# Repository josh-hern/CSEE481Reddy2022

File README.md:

# CSEE481Reddy2022
Group repo for WVU capstone 2022

## infrastructure

Contains the database, REST API, and business logic. Implemented in Python.

## hardware

Contains the main board PCB, ESP 32 symbol library, and 3D files.

## webview

Contains the web application that will be used to server web clients of the
battleship game.

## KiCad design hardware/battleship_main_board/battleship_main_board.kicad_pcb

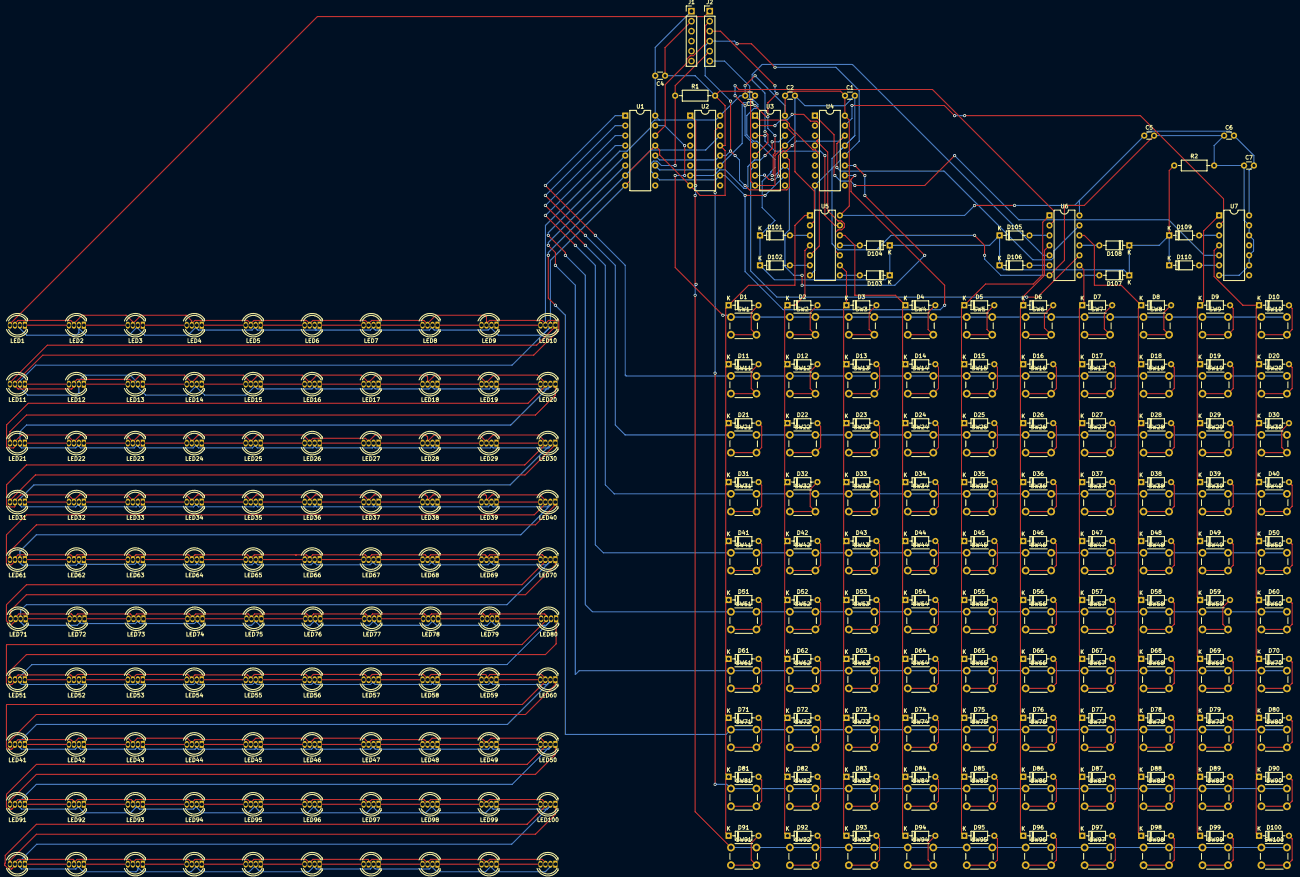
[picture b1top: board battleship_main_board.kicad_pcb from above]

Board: 2 copper layers, 328 parts (0 on the bottom side), 248 nets.

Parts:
C1, C2, C3, C4, C5, C6, C7: 0.1uf; C_Disc_D3.0mm_W1.6mm_P2.50mm
D1, D2, D3, D4, D5, D6, D7, D8, D9, D10, D11, D12, D13, D14, D15, D16, D17, D18, D19, D20, D21, D22, D23, D24, D25, D26, D27, D28, D29, D30, D31, D32, D33, D34, D35, D36, D37, D38, D39, D40, D41, D42, D43, D44, D45, D46, D47, D48, D49, D50, D51, D52, D53, D54, D55, D56, D57, D58, D59, D60, D61, D62, D63, D64, D65, D66, D67, D68, D69, D70, D71, D72, D73, D74, D75, D76, D77, D78, D79, D80, D81, D82, D83, D84, D85, D86, D87, D88, D89, D90, D91, D92, D93, D94, D95, D96, D97, D98, D99, D100, D101, D102, D103, D104, D105, D106, D107, D108, D109, D110: 1N4148; D_DO-35_SOD27_P7.62mm_Horizontal
J1, J2: Conn_01x06; PinHeader_1x06_P2.54mm_Vertical
LED1, LED2, LED3, LED4, LED5, LED6, LED7, LED8, LED9, LED10, LED11, LED12, LED13, LED14, LED15, LED16, LED17, LED18, LED19, LED20, LED21, LED22, LED23, LED24, LED25, LED26, LED27, LED28, LED29, LED30, LED31, LED32, LED33, LED34, LED35, LED36, LED37, LED38, LED39, LED40, LED41, LED42, LED43, LED44, LED45, LED46, LED47, LED48, LED49, LED50, LED51, LED52, LED53, LED54, LED55, LED56, LED57, LED58, LED59, LED60, LED61, LED62, LED63, LED64, LED65, LED66, LED67, LED68, LED69, LED70, LED71, LED72, LED73, LED74, LED75, LED76, LED77, LED78, LED79, LED80, LED81, LED82, LED83, LED84, LED85, LED86, LED87, LED88, LED89, LED90, LED91, LED92, LED93, LED94, LED95, LED96, LED97, LED98, LED99, LED100: WS2812B; LED_D5.0mm-4_RGB
R1, R2: 1k; R_Axial_DIN0207_L6.3mm_D2.5mm_P10.16mm_Horizontal
SW1, SW2, SW3, SW4, SW5, SW6, SW7, SW8, SW9, SW10, SW11, SW12, SW13, SW14, SW15, SW16, SW17, SW18, SW19, SW20, SW21, SW22, SW23, SW24, SW25, SW26, SW27, SW28, SW29, SW30, SW31, SW32, SW33, SW34, SW35, SW36, SW37, SW38, SW39, SW40, SW41, SW42, SW43, SW44, SW45, SW46, SW47, SW48, SW49, SW50, SW51, SW52, SW53, SW54, SW55, SW56, SW57, SW58, SW59, SW60, SW61, SW62, SW63, SW64, SW65, SW66, SW67, SW68, SW69, SW70, SW71, SW72, SW73, SW74, SW75, SW76, SW77, SW78, SW79, SW80, SW81, SW82, SW83, SW84, SW85, SW86, SW87, SW88, SW89, SW90, SW91, SW92, SW93, SW94, SW95, SW96, SW97, SW98, SW99, SW100: SW_Push; SW_PUSH_6mm
U1, U2, U3, U4: 74HC595; DIP-16_W7.62mm
U5, U6, U7: 74LS08; DIP-14_W7.62mm

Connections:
+5V: C1.1, C2.1, C3.2, C4.2, C5.1, C6.2, C7.2, J1.1, LED1.3 (VDD), LED2.3 (VDD), LED3.3 (VDD), LED4.3 (VDD), LED5.3 (VDD), LED6.3 (VDD), LED7.3 (VDD), LED8.3 (VDD), LED9.3 (VDD), LED10.3 (VDD), LED11.3 (VDD), LED12.3 (VDD), LED13.3 (VDD), LED14.3 (VDD), LED15.3 (VDD), LED16.3 (VDD), LED17.3 (VDD), LED18.3 (VDD), LED19.3 (VDD), LED20.3 (VDD), LED21.3 (VDD), LED22.3 (VDD), LED23.3 (VDD), LED24.3 (VDD), LED25.3 (VDD), LED26.3 (VDD), LED27.3 (VDD), LED28.3 (VDD), LED29.3 (VDD), LED30.3 (VDD), LED31.3 (VDD), LED32.3 (VDD), LED33.3 (VDD), LED34.3 (VDD), LED35.3 (VDD), LED36.3 (VDD), LED37.3 (VDD), LED38.3 (VDD), LED39.3 (VDD), LED40.3 (VDD), LED41.3 (VDD), LED42.3 (VDD), LED43.3 (VDD), LED44.3 (VDD), LED45.3 (VDD), LED46.3 (VDD), LED47.3 (VDD), LED48.3 (VDD), LED49.3 (VDD), LED50.3 (VDD), LED51.3 (VDD), LED52.3 (VDD), LED53.3 (VDD), LED54.3 (VDD), LED55.3 (VDD), LED56.3 (VDD), LED57.3 (VDD), LED58.3 (VDD), LED59.3 (VDD), LED60.3 (VDD), LED61.3 (VDD), LED62.3 (VDD), LED63.3 (VDD), LED64.3 (VDD), LED65.3 (VDD), LED66.3 (VDD), LED67.3 (VDD), LED68.3 (VDD), LED69.3 (VDD), LED70.3 (VDD), LED71.3 (VDD), LED72.3 (VDD), LED73.3 (VDD), LED74.3 (VDD), LED75.3 (VDD), LED76.3 (VDD), LED77.3 (VDD), LED78.3 (VDD), LED79.3 (VDD), LED80.3 (VDD), LED81.3 (VDD), LED82.3 (VDD), LED83.3 (VDD), LED84.3 (VDD), LED85.3 (VDD), LED86.3 (VDD), LED87.3 (VDD), LED88.3 (VDD), LED89.3 (VDD), LED90.3 (VDD), LED91.3 (VDD), LED92.3 (VDD), LED93.3 (VDD), LED94.3 (VDD), LED95.3 (VDD), LED96.3 (VDD), LED97.3 (VDD), LED98.3 (VDD), LED99.3 (VDD), LED100.3 (VDD), U1.16 (VCC), U2.16 (VCC), U3.16 (VCC), U4.16 (VCC), U5.14 (VCC), U6.14 (VCC), U7.14 (VCC)
/ESP32/ButtonPressedIn: D101.1 (K), D102.1 (K), D103.1 (K), D104.1 (K), D105.1 (K), D106.1 (K), D107.1 (K), D108.1 (K), D109.1 (K), D110.1 (K), J2.6, R2.1
/ESP32/Clr: J2.5, R1.1, U1.10 (~SRCLR), U2.10 (~SRCLR), U3.10 (~SRCLR), U4.10 (~SRCLR)
/ESP32/LED_out: J2.1, LED1.4 (DIN)
/ESP32/RegClock: J2.4, U1.12 (RCLK), U2.12 (RCLK), U3.12 (RCLK), U4.12 (RCLK)
/ESP32/SerialOutput: J2.2, U1.14 (SER)
/ESP32/ShiftClock: J2.3, U1.11 (SRCLK), U2.11 (SRCLK), U3.11 (SRCLK), U4.11 (SRCLK)
/OutputMatrix1/TenLEDRow1/Row_data_out: LED20.1 (DOUT), LED21.4 (DIN)
/OutputMatrix1/TenLEDRow2/Row_data_out: LED30.1 (DOUT), LED31.4 (DIN)
/OutputMatrix1/TenLEDRow3/Row_data_out: LED40.1 (DOUT), LED61.4 (DIN)
/OutputMatrix1/TenLEDRow4/Row_data_in: LED41.4 (DIN), LED60.1 (DOUT)
/OutputMatrix1/TenLEDRow4/Row_data_out: LED50.1 (DOUT), LED91.4 (DIN)
/OutputMatrix1/TenLEDRow5/Row_data_in: LED51.4 (DIN), LED80.1 (DOUT)
/OutputMatrix1/TenLEDRow6/Row_data_out: LED70.1 (DOUT), LED71.4 (DIN)
/OutputMatrix1/TenLEDRow8/Row_data_in: LED81.4 (DIN), LED100.1 (DOUT)
/OutputMatrix1/TenLEDRow/Row_data_out: LED10.1 (DOUT), LED11.4 (DIN)
/UserInputs/InputMatrix1/Button Row1/ColumnIn3: D4.1 (K), D14.1 (K), D24.1 (K), D34.1 (K), D44.1 (K), D54.1 (K), D64.1 (K), D74.1 (K), D84.1 (K), D94.1 (K), U5.12
/UserInputs/InputMatrix1/Button Row1/ColumnIn4: D5.1 (K), D15.1 (K), D25.1 (K), D35.1 (K), D45.1 (K), D55.1 (K), D65.1 (K), D75.1 (K), D85.1 (K), D95.1 (K), U6.1
/UserInputs/InputMatrix1/Button Row1/ColumnIn5: D6.1 (K), D16.1 (K), D26.1 (K), D36.1 (K), D46.1 (K), D56.1 (K), D66.1 (K), D76.1 (K), D86.1 (K), D96.1 (K), U6.4
/UserInputs/InputMatrix1/Button Row1/ColumnIn6: D7.1 (K), D17.1 (K), D27.1 (K), D37.1 (K), D47.1 (K), D57.1 (K), D67.1 (K), D77.1 (K), D87.1 (K), D97.1 (K), U6.9
/UserInputs/InputMatrix1/Button Row1/ColumnIn8: D9.1 (K), D19.1 (K), D29.1 (K), D39.1 (K), D49.1 (K), D59.1 (K), D69.1 (K), D79.1 (K), D89.1 (K), D99.1 (K), U7.1
/UserInputs/InputMatrix1/Button Row1/ColumnIn9: D10.1 (K), D20.1 (K), D30.1 (K), D40.1 (K), D50.1 (K), D60.1 (K), D70.1 (K), D80.1 (K), D90.1 (K), D100.1 (K), U7.4
/UserInputs/InputMatrix1/Button Row1/ColumnOut0: D1.1 (K), D11.1 (K), D21.1 (K), D31.1 (K), D41.1 (K), D51.1 (K), D61.1 (K), D71.1 (K), D81.1 (K), D91.1 (K), U5.1
/UserInputs/InputMatrix1/Button Row1/ColumnOut1: D2.1 (K), D12.1 (K), D22.1 (K), D32.1 (K), D42.1 (K), D52.1 (K), D62.1 (K), D72.1 (K), D82.1 (K), D92.1 (K), U5.4
/UserInputs/InputMatrix1/Button Row1/ColumnOut2: D3.1 (K), D13.1 (K), D23.1 (K), D33.1 (K), D43.1 (K), D53.1 (K), D63.1 (K), D73.1 (K), D83.1 (K), D93.1 (K), U5.9
/UserInputs/InputMatrix1/Button Row1/ColumnOut7: D8.1 (K), D18.1 (K), D28.1 (K), D38.1 (K), D48.1 (K), D58.1 (K), D68.1 (K), D78.1 (K), D88.1 (K), D98.1 (K), U6.12
/UserInputs/InputMatrix1/Col0: U3.15 (QA), U5.2
/UserInputs/InputMatrix1/Col1: U3.1 (QB), U5.5
/UserInputs/InputMatrix1/Col2: U3.2 (QC), U5.10
/UserInputs/InputMatrix1/Col3: U3.3 (QD), U5.13
/UserInputs/InputMatrix1/Col4: U3.4 (QE), U6.2
/UserInputs/InputMatrix1/Col5: U3.5 (QF), U6.5
/UserInputs/InputMatrix1/Col6: U3.6 (QG), U6.10
/UserInputs/InputMatrix1/Col7: U3.7 (QH), U4.14 (SER), U6.13
/UserInputs/InputMatrix1/Col8: U4.15 (QA), U7.2
/UserInputs/InputMatrix1/Col9: U4.1 (QB), U7.5
/UserInputs/InputMatrix1/Row0: SW1.1, SW2.1, SW3.1, SW4.1, SW5.1, SW6.1, SW7.1, SW8.1, SW9.1, SW10.1, U1.15 (QA)
/UserInputs/InputMatrix1/Row1: SW11.1, SW12.1, SW13.1, SW14.1, SW15.1, SW16.1, SW17.1, SW18.1, SW19.1, SW20.1, U1.1 (QB)
/UserInputs/InputMatrix1/Row2: SW21.1, SW22.1, SW23.1, SW24.1, SW25.1, SW26.1, SW27.1, SW28.1, SW29.1, SW30.1, U1.2 (QC)
/UserInputs/InputMatrix1/Row3: SW31.1, SW32.1, SW33.1, SW34.1, SW35.1, SW36.1, SW37.1, SW38.1, SW39.1, SW40.1, U1.3 (QD)
/UserInputs/InputMatrix1/Row4: SW41.1, SW42.1, SW43.1, SW44.1, SW45.1, SW46.1, SW47.1, SW48.1, SW49.1, SW50.1, U1.4 (QE)
/UserInputs/InputMatrix1/Row5: SW51.1, SW52.1, SW53.1, SW54.1, SW55.1, SW56.1, SW57.1, SW58.1, SW59.1, SW60.1, U1.5 (QF)
/UserInputs/InputMatrix1/Row6: SW61.1, SW62.1, SW63.1, SW64.1, SW65.1, SW66.1, SW67.1, SW68.1, SW69.1, SW70.1, U1.6 (QG)
/UserInputs/InputMatrix1/Row7: SW71.1, SW72.1, SW73.1, SW74.1, SW75.1, SW76.1, SW77.1, SW78.1, SW79.1, SW80.1, U1.7 (QH), U2.14 (SER)
/UserInputs/InputMatrix1/Row8: SW81.1, SW82.1, SW83.1, SW84.1, SW85.1, SW86.1, SW87.1, SW88.1, SW89.1, SW90.1, U2.15 (QA)
/UserInputs/InputMatrix1/Row9: SW91.1, SW92.1, SW93.1, SW94.1, SW95.1, SW96.1, SW97.1, SW98.1, SW99.1, SW100.1, U2.1 (QB)
GNDREF: C1.2, C2.2, C3.1, C4.1, C5.2, C6.1, C7.1, J1.2, LED1.2 (GND), LED2.2 (GND), LED3.2 (GND), LED4.2 (GND), LED5.2 (GND), LED6.2 (GND), LED7.2 (GND), LED8.2 (GND), LED9.2 (GND), LED10.2 (GND), LED11.2 (GND), LED12.2 (GND), LED13.2 (GND), LED14.2 (GND), LED15.2 (GND), LED16.2 (GND), LED17.2 (GND), LED18.2 (GND), LED19.2 (GND), LED20.2 (GND), LED21.2 (GND), LED22.2 (GND), LED23.2 (GND), LED24.2 (GND), LED25.2 (GND), LED26.2 (GND), LED27.2 (GND), LED28.2 (GND), LED29.2 (GND), LED30.2 (GND), LED31.2 (GND), LED32.2 (GND), LED33.2 (GND), LED34.2 (GND), LED35.2 (GND), LED36.2 (GND), LED37.2 (GND), LED38.2 (GND), LED39.2 (GND), LED40.2 (GND), LED41.2 (GND), LED42.2 (GND), LED43.2 (GND), LED44.2 (GND), LED45.2 (GND), LED46.2 (GND), LED47.2 (GND), LED48.2 (GND), LED49.2 (GND), LED50.2 (GND), LED51.2 (GND), LED52.2 (GND), LED53.2 (GND), LED54.2 (GND), LED55.2 (GND), LED56.2 (GND), LED57.2 (GND), LED58.2 (GND), LED59.2 (GND), LED60.2 (GND), LED61.2 (GND), LED62.2 (GND), LED63.2 (GND), LED64.2 (GND), LED65.2 (GND), LED66.2 (GND), LED67.2 (GND), LED68.2 (GND), LED69.2 (GND), LED70.2 (GND), LED71.2 (GND), LED72.2 (GND), LED73.2 (GND), LED74.2 (GND), LED75.2 (GND), LED76.2 (GND), LED77.2 (GND), LED78.2 (GND), LED79.2 (GND), LED80.2 (GND), LED81.2 (GND), LED82.2 (GND), LED83.2 (GND), LED84.2 (GND), LED85.2 (GND), LED86.2 (GND), LED87.2 (GND), LED88.2 (GND), LED89.2 (GND), LED90.2 (GND), LED91.2 (GND), LED92.2 (GND), LED93.2 (GND), LED94.2 (GND), LED95.2 (GND), LED96.2 (GND), LED97.2 (GND), LED98.2 (GND), LED99.2 (GND), LED100.2 (GND), R1.2, R2.2, U1.8 (GND), U1.13 (~OE), U2.8 (GND), U2.13 (~OE), U3.8 (GND), U3.13 (~OE), U4.8 (GND), U4.13 (~OE), U5.7 (GND), U6.7 (GND), U7.7 (GND), U7.9, U7.10, U7.12, U7.13
unnamed: D1.2 (A), SW1.2
unnamed: D2.2 (A), SW2.2
unnamed: D3.2 (A), SW3.2
unnamed: D4.2 (A), SW4.2
unnamed: D5.2 (A), SW5.2
unnamed: D6.2 (A), SW6.2
unnamed: D7.2 (A), SW7.2
unnamed: D8.2 (A), SW8.2
unnamed: D9.2 (A), SW9.2
unnamed: D10.2 (A), SW10.2
unnamed: D11.2 (A), SW11.2
unnamed: D12.2 (A), SW12.2
unnamed: D13.2 (A), SW13.2
unnamed: D14.2 (A), SW14.2
unnamed: D15.2 (A), SW15.2
unnamed: D16.2 (A), SW16.2
unnamed: D17.2 (A), SW17.2
unnamed: D18.2 (A), SW18.2
unnamed: D19.2 (A), SW19.2
unnamed: D20.2 (A), SW20.2
unnamed: D21.2 (A), SW21.2
unnamed: D22.2 (A), SW22.2
unnamed: D23.2 (A), SW23.2
unnamed: D24.2 (A), SW24.2
unnamed: D25.2 (A), SW25.2
unnamed: D26.2 (A), SW26.2
unnamed: D27.2 (A), SW27.2
unnamed: D28.2 (A), SW28.2
unnamed: D29.2 (A), SW29.2
unnamed: D30.2 (A), SW30.2
unnamed: D31.2 (A), SW31.2
unnamed: D32.2 (A), SW32.2
unnamed: D33.2 (A), SW33.2
unnamed: D34.2 (A), SW34.2
unnamed: D35.2 (A), SW35.2
unnamed: D36.2 (A), SW36.2
unnamed: D37.2 (A), SW37.2
unnamed: D38.2 (A), SW38.2
unnamed: D39.2 (A), SW39.2
unnamed: D40.2 (A), SW40.2
unnamed: D41.2 (A), SW41.2
unnamed: D42.2 (A), SW42.2
unnamed: D43.2 (A), SW43.2
unnamed: D44.2 (A), SW44.2
unnamed: D45.2 (A), SW45.2
unnamed: D46.2 (A), SW46.2
unnamed: D47.2 (A), SW47.2
unnamed: D48.2 (A), SW48.2
unnamed: D49.2 (A), SW49.2
unnamed: D50.2 (A), SW50.2
unnamed: D51.2 (A), SW51.2
unnamed: D52.2 (A), SW52.2
unnamed: D53.2 (A), SW53.2
unnamed: D54.2 (A), SW54.2
unnamed: D55.2 (A), SW55.2
unnamed: D56.2 (A), SW56.2
unnamed: D57.2 (A), SW57.2
unnamed: D58.2 (A), SW58.2
unnamed: D59.2 (A), SW59.2
unnamed: D60.2 (A), SW60.2
unnamed: D61.2 (A), SW61.2
unnamed: D62.2 (A), SW62.2
unnamed: D63.2 (A), SW63.2
unnamed: D64.2 (A), SW64.2
unnamed: D65.2 (A), SW65.2
unnamed: D66.2 (A), SW66.2
unnamed: D67.2 (A), SW67.2
unnamed: D68.2 (A), SW68.2
unnamed: D69.2 (A), SW69.2
unnamed: D70.2 (A), SW70.2
unnamed: D71.2 (A), SW71.2
unnamed: D72.2 (A), SW72.2
unnamed: D73.2 (A), SW73.2
unnamed: D74.2 (A), SW74.2
unnamed: D75.2 (A), SW75.2
unnamed: D76.2 (A), SW76.2
unnamed: D77.2 (A), SW77.2
unnamed: D78.2 (A), SW78.2
unnamed: D79.2 (A), SW79.2
unnamed: D80.2 (A), SW80.2
unnamed: D81.2 (A), SW81.2
unnamed: D82.2 (A), SW82.2
unnamed: D83.2 (A), SW83.2
unnamed: D84.2 (A), SW84.2
unnamed: D85.2 (A), SW85.2
unnamed: D86.2 (A), SW86.2
unnamed: D87.2 (A), SW87.2
unnamed: D88.2 (A), SW88.2
unnamed: D89.2 (A), SW89.2
unnamed: D90.2 (A), SW90.2
unnamed: D91.2 (A), SW91.2
unnamed: D92.2 (A), SW92.2
unnamed: D93.2 (A), SW93.2
unnamed: D94.2 (A), SW94.2
unnamed: D95.2 (A), SW95.2
unnamed: D96.2 (A), SW96.2
unnamed: D97.2 (A), SW97.2
unnamed: D98.2 (A), SW98.2
unnamed: D99.2 (A), SW99.2
unnamed: D100.2 (A), SW100.2
unnamed: D101.2 (A), U5.3
unnamed: D102.2 (A), U5.6
unnamed: D103.2 (A), U5.8
unnamed: D104.2 (A), U5.11
unnamed: D105.2 (A), U6.3
unnamed: D106.2 (A), U6.6
unnamed: D107.2 (A), U6.8
unnamed: D108.2 (A), U6.11
unnamed: D109.2 (A), U7.3
unnamed: D110.2 (A), U7.6
unnamed: LED1.1 (DOUT), LED2.4 (DIN)
unnamed: LED2.1 (DOUT), LED3.4 (DIN)
unnamed: LED3.1 (DOUT), LED4.4 (DIN)
unnamed: LED4.1 (DOUT), LED5.4 (DIN)
unnamed: LED5.1 (DOUT), LED6.4 (DIN)
unnamed: LED6.1 (DOUT), LED7.4 (DIN)
unnamed: LED7.1 (DOUT), LED8.4 (DIN)
unnamed: LED8.1 (DOUT), LED9.4 (DIN)
unnamed: LED9.1 (DOUT), LED10.4 (DIN)
unnamed: LED11.1 (DOUT), LED12.4 (DIN)
unnamed: LED12.1 (DOUT), LED13.4 (DIN)
unnamed: LED13.1 (DOUT), LED14.4 (DIN)
unnamed: LED14.1 (DOUT), LED15.4 (DIN)
unnamed: LED15.1 (DOUT), LED16.4 (DIN)
unnamed: LED16.1 (DOUT), LED17.4 (DIN)
unnamed: LED17.1 (DOUT), LED18.4 (DIN)
unnamed: LED18.1 (DOUT), LED19.4 (DIN)
unnamed: LED19.1 (DOUT), LED20.4 (DIN)
unnamed: LED21.1 (DOUT), LED22.4 (DIN)
unnamed: LED22.1 (DOUT), LED23.4 (DIN)
unnamed: LED23.1 (DOUT), LED24.4 (DIN)
unnamed: LED24.1 (DOUT), LED25.4 (DIN)
unnamed: LED25.1 (DOUT), LED26.4 (DIN)
unnamed: LED26.1 (DOUT), LED27.4 (DIN)
unnamed: LED27.1 (DOUT), LED28.4 (DIN)
unnamed: LED28.1 (DOUT), LED29.4 (DIN)
unnamed: LED29.1 (DOUT), LED30.4 (DIN)
unnamed: LED31.1 (DOUT), LED32.4 (DIN)
unnamed: LED32.1 (DOUT), LED33.4 (DIN)
unnamed: LED33.1 (DOUT), LED34.4 (DIN)
unnamed: LED34.1 (DOUT), LED35.4 (DIN)
unnamed: LED35.1 (DOUT), LED36.4 (DIN)
unnamed: LED36.1 (DOUT), LED37.4 (DIN)
unnamed: LED37.1 (DOUT), LED38.4 (DIN)
unnamed: LED38.1 (DOUT), LED39.4 (DIN)
unnamed: LED39.1 (DOUT), LED40.4 (DIN)
unnamed: LED41.1 (DOUT), LED42.4 (DIN)
unnamed: LED42.1 (DOUT), LED43.4 (DIN)
unnamed: LED43.1 (DOUT), LED44.4 (DIN)
unnamed: LED44.1 (DOUT), LED45.4 (DIN)
unnamed: LED45.1 (DOUT), LED46.4 (DIN)
unnamed: LED46.1 (DOUT), LED47.4 (DIN)
unnamed: LED47.1 (DOUT), LED48.4 (DIN)
unnamed: LED48.1 (DOUT), LED49.4 (DIN)
unnamed: LED49.1 (DOUT), LED50.4 (DIN)
unnamed: LED51.1 (DOUT), LED52.4 (DIN)
unnamed: LED52.1 (DOUT), LED53.4 (DIN)
unnamed: LED53.1 (DOUT), LED54.4 (DIN)
unnamed: LED54.1 (DOUT), LED55.4 (DIN)
unnamed: LED55.1 (DOUT), LED56.4 (DIN)
unnamed: LED56.1 (DOUT), LED57.4 (DIN)
unnamed: LED57.1 (DOUT), LED58.4 (DIN)
unnamed: LED58.1 (DOUT), LED59.4 (DIN)
unnamed: LED59.1 (DOUT), LED60.4 (DIN)
unnamed: LED61.1 (DOUT), LED62.4 (DIN)
unnamed: LED62.1 (DOUT), LED63.4 (DIN)
unnamed: LED63.1 (DOUT), LED64.4 (DIN)
unnamed: LED64.1 (DOUT), LED65.4 (DIN)
unnamed: LED65.1 (DOUT), LED66.4 (DIN)
unnamed: LED66.1 (DOUT), LED67.4 (DIN)
unnamed: LED67.1 (DOUT), LED68.4 (DIN)
unnamed: LED68.1 (DOUT), LED69.4 (DIN)
unnamed: LED69.1 (DOUT), LED70.4 (DIN)
unnamed: LED71.1 (DOUT), LED72.4 (DIN)
unnamed: LED72.1 (DOUT), LED73.4 (DIN)
unnamed: LED73.1 (DOUT), LED74.4 (DIN)
unnamed: LED74.1 (DOUT), LED75.4 (DIN)
unnamed: LED75.1 (DOUT), LED76.4 (DIN)
unnamed: LED76.1 (DOUT), LED77.4 (DIN)
unnamed: LED77.1 (DOUT), LED78.4 (DIN)
unnamed: LED78.1 (DOUT), LED79.4 (DIN)
unnamed: LED79.1 (DOUT), LED80.4 (DIN)
unnamed: LED81.1 (DOUT), LED82.4 (DIN)
unnamed: LED82.1 (DOUT), LED83.4 (DIN)
unnamed: LED83.1 (DOUT), LED84.4 (DIN)
unnamed: LED84.1 (DOUT), LED85.4 (DIN)
unnamed: LED85.1 (DOUT), LED86.4 (DIN)
unnamed: LED86.1 (DOUT), LED87.4 (DIN)
unnamed: LED87.1 (DOUT), LED88.4 (DIN)
unnamed: LED88.1 (DOUT), LED89.4 (DIN)
unnamed: LED89.1 (DOUT), LED90.4 (DIN)
unnamed: LED91.1 (DOUT), LED92.4 (DIN)
unnamed: LED92.1 (DOUT), LED93.4 (DIN)
unnamed: LED93.1 (DOUT), LED94.4 (DIN)
unnamed: LED94.1 (DOUT), LED95.4 (DIN)
unnamed: LED95.1 (DOUT), LED96.4 (DIN)
unnamed: LED96.1 (DOUT), LED97.4 (DIN)
unnamed: LED97.1 (DOUT), LED98.4 (DIN)
unnamed: LED98.1 (DOUT), LED99.4 (DIN)
unnamed: LED99.1 (DOUT), LED100.4 (DIN)
unnamed: U2.7 (QH), U3.14 (SER)

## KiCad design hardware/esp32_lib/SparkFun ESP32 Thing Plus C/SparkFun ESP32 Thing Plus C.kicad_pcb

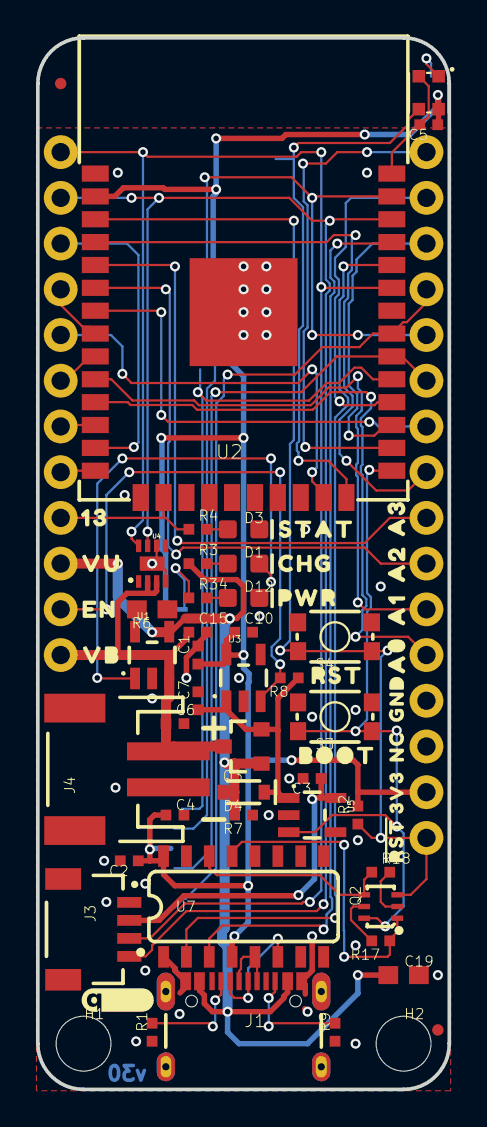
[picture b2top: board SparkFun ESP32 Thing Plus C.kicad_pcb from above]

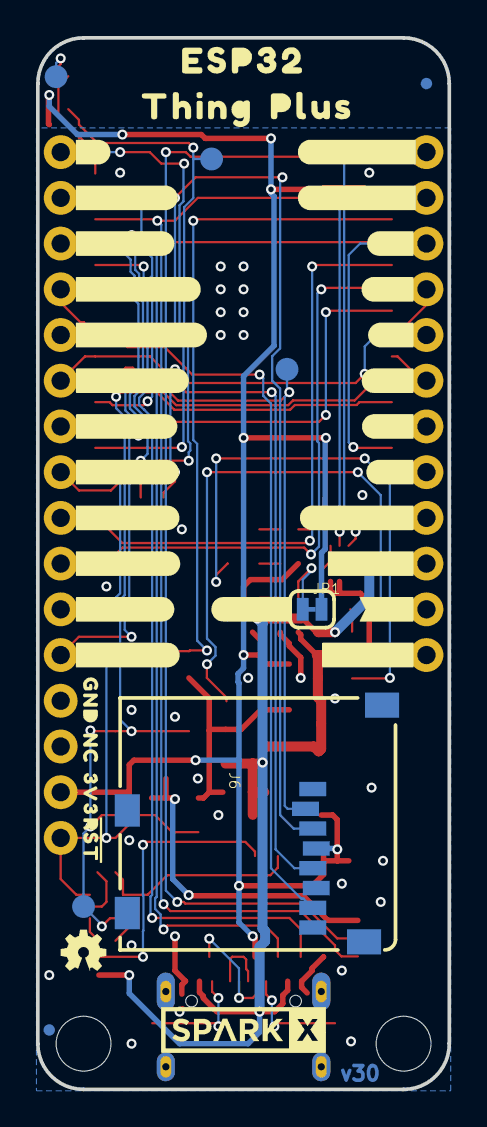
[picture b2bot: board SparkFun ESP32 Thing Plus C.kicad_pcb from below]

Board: 2 copper layers, 22.9 x 58.4 mm, 106 parts (42 on the bottom side), 49 nets.

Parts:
C1: 10uF; 0402-TIGHT
C2, C4, C5, C15: 0.1uF; 0402-TIGHT
C3, C7, C10: 1.0uF; 0402-TIGHT
C6: 4.7uF; 0402-TIGHT
C19: 4.7uF; 0603
D1: Yellow; LED-0603
D3: BLUE; LED-0603
D4: 3A/10V/280mV; SOD-323
D5: WS2812; WS2812-2020
D12: RED; LED-0603
FD1, FD2, FD3, FD4: FIDUCIALUFIDUCIAL; FIDUCIAL-MICRO
FRAME1: FRAME-LEDGER; CREATIVE_COMMONS
H1, H2: STAND-OFFTIGHT; STAND-OFF-TIGHT
J1: USB-C-16P-2LAYER-PADS
J3: QWIIC_RIGHT_ANGLE; JST04_1MM_RA
J4: JST-2-SMD
J6: microSD; MICRO-SD-SOCKET
JP1: SMT-JUMPER_2_NC_TRACE_SILK
LOGO2: OSHW-LOGOMINI; OSHW-LOGO-MINI
LOGO4: QWIIC_LOGO_4MM; QWIIC_4MM
Q2: MBT3904DW1T1; SC70-6
Q3: 20V/4.2A/52mΩ/1.4W; SOT23-3
R2, R7, R8, R17, R18: 10k; 0402-TIGHT
R3, R4, R34: 1k; 0402-TIGHT
R6: 2.0k; 0603
R9, R10: 5.1k; 0402-TIGHT
S3: Boot; TACTILE_SWITCH_SMD_4.6X2.8MM
S4: Reset; TACTILE_SWITCH_SMD_4.6X2.8MM
TP1, TP2, TP3, TP4: PAD.03X.05
U1: MCP73831; SOT23-5
U2: ESP-WROOM-32NARROW; ESP-WROOM-32-NARROW
U3, U5: AP2112K-3.3; SOT23-5
U4: MAX17048; DFN-8
U6: THINGPLUS_LOGICAL; THINGPLUS_FOOTPRINT
U7: CH340C; SO016
U$1: SPARKX-LOGO4; SPARKX-MEDIUM
U$23, U$108: 3V30
U$24: CHG1
U$25: PWR2
U$26: STAT0
U$56, U$75: GND1
U$57: #4#0
U$59: ORDERING_INSTRUCTIONS
U$62: #23#COPI#0
U$68: A03
U$69: A12
U$70: A21
U$71: A30
U$72: #17#TX#0
U$73: VB1
U$74: EN3
U$76: VU0
U$77: 130
U$78: BOOT0
U$79, U$109: #RST#0
U$80: RST0
U$81: #16#RX#0
U$82: #19#CIPO#0
U$83: #18#SCK#0
U$84: #35#A5#0
U$85: #36#A4#0
U$86: #25#A1#2
U$87: #26#A0#3
U$88: #34#A2#1
U$89: #39#A3#0
U$90: #12#4
U$91: #14#9
U$92: #15#7
U$93: #27#5
U$94: #32#8
U$95: #33#6
U$96: #EN#1
U$97: #VBAT#0
U$98: #VUSB#2
U$99: #13#LED#0
U$100: #21#SDA#1
U$101: #22#SCL#0
U$102: #PWR#0
U$103: ESP320
U$104: THING1
U$105: PLUS2
U$106, U$107: NC0

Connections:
3.3V: C1.1, C2.1, C4.1, C5.1, C10.1, D5.VCC, J6.VCC, JP1.2, R2.2, U2.2, U3.5, U6.3V3, U7.4, U7.16
CH340-DTR: Q2.1, R17.1, U7.13
CH340-RTS: Q2.4, R18.1, U7.14
CH340-RX: U2.35, U7.3
CH340-TX: U2.34, U7.2
CHG: D1.C, U1.1
CHG_LED: D1.A, R3.2
D+: J1.A6, J1.B6, U7.5
D-: J1.A7, J1.B7, U7.6
DTR-10K: Q2.5, R17.2
ESP_0/QPWR: Q2.6, S3.3, S3.4, TP1.P$1, U2.25, U5.3
ESP_2/RGB_DI: D5.DI, TP3.P$1, U2.24
ESP_4/TP_FB: U2.26, U6.FREEBIE
ESP_5/SD_CS: J6.CS/DAT3, TP4.P$1, U2.29
ESP_12/TP_12: U2.14, U6.12
ESP_13/TP_13/LED: R4.1, U2.16, U6.13
ESP_14/TP_7: U2.13, U6.7
ESP_15/TP_9: U2.23, U6.9
ESP_16/TP_RX: U2.27, U6.RX
ESP_17/TP_TX: U2.28, U6.TX
ESP_18/TP_SCK: J6.SCLK, U2.30, U6.SCK
ESP_19/TP_CIPO: J6.DO/DAT0, U2.31, U6.CIPO
ESP_21/TP_SDA: J3.3, U2.33, U4.8, U6.SDA
ESP_22/TP_SCL: J3.4, U2.36, U4.7, U6.SCL
ESP_23/TP_COPI: J6.DI/CMD, U2.37, U6.COPI
ESP_25/TP_A1: U2.10, U6.A1
ESP_26/TP_A0: U2.11, U6.A0
ESP_27/TP_11: U2.12, U6.11
ESP_32/TP_8: U2.8, U6.8
ESP_33/TP_10: U2.9, U6.10
ESP_34/TP_A2: U2.6, U6.A2
ESP_35/TP_A5: U2.7, U6.A5
ESP_36/TP_A4: U2.4, U6.A4
ESP_39/TP_A3: U2.5, U6.A3
GND: C1.2, C2.2, C3.2, C4.2, C5.2, C6.2, C7.2, C10.2, C15.2, C19.2, D3.C, D5.GND, D12.C, J1.GND, J1.GND2, J3.1, J4.1, J6.CD1, J6.GND, J6.GND1, J6.GND3, R6.1, R7.1, R9.1, R10.1, S3.1, S3.2, S4.1, S4.2, U1.2, U2.1, U2.15, U2.38, U2.GND, U3.2, U4.1, U4.4, U4.6, U4.9, U5.2, U6.GND, U7.1
unnamed: JP1.1, R34.1
unnamed: D3.A, R4.2
unnamed: D5.DO, TP2.P$1
unnamed: J1.B5, R9.2
unnamed: J1.A5, R10.2
unnamed: R6.2, U1.5
unnamed: D12.A, R34.2
QWIIC_PWR: C3.1, J3.2, U5.5
RTS-10K: Q2.2, R18.2
TP_EN: R8.2, U3.3, U6.EN
VIN: C7.1, D4.C, Q3.2, R8.1, U3.1, U5.1
V_BATT: C6.1, C15.1, J4.2, Q3.3, U1.3, U4.2, U4.3, U6.V_BATT
V_USB: C19.1, D4.A, J1.VBUS1, J1.VBUS2, Q3.1, R3.1, R7.2, U1.4, U6.V_USB
~RESET: Q2.3, R2.1, S4.3, S4.4, U2.3, U6.RST

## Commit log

2022-01-24 Made a few folders for files
2022-01-24 quick skeleton for database stuff
2022-01-24 moved construct_database class to its own file
2022-01-25 Now creates databases
2022-01-25 tried to add rows to database, but was unsuccessful
2022-01-29 finished initialization of database
2022-01-29 added option to remove all data in nuke_tables.py
2022-01-29 added some more blank methods to the interface
2022-01-29 test with verifying commit
2022-01-29 test with verifying commit, again
2022-01-31 remade methods in database_query_insert.py into class
2022-01-31 forgot to rename a few things, and added newline at end of file
2022-01-31 create new folders/ rename
2022-01-31 update gitignore
2022-01-31 started pipenv
2022-01-31 rename folder
2022-02-07 preparatory commit before database restructuring
2022-02-07 added new tables to construct_database.py, and removed old ones
2022-02-07 updated nuke_tables.py to have correct directory path
2022-02-07 updated database_query_insert.py to insert basic data into new tables
    Also updated a few necessary lines in construct_database.py
2022-02-07 added more general method by which to call other initialization methods
    This should help in the future if we initialize more tables
2022-02-07 added README.md file for models directory, so that the organization is more clear
2022-02-07 Added `isHit` column to AttackMoves table
2022-02-07 reorganized structure a bit to use directories like libraries
2022-02-10 Changed dir ESP32_stuff to hardware
2022-02-10 Refactored directory structure
2022-02-10 Fixed README file syntax
2022-02-11 fixed small import issue, where reordering folders made importing between them not work
2022-02-20 interface progress, and some extra fixes for constructing the database
2022-02-20 continuing progress on insertion into database
2022-02-21 restructure, sorry everyone :(
2022-02-21 setup env
2022-02-21 setup api + webpage serving
2022-02-25 removed ESPConnector Class, because it was unnecessary
2022-02-25 modified imports to reflect new folders
2022-02-25 one last import to change
2022-02-25 changed database location to make more sense
2022-02-25 and added database to .gitignore, so that we don't share it every time
2022-02-28 made it work with real SQL query, will be trying with ORM
2022-03-01 continued work on attack checks
2022-03-01 added methods to check if a space has already been attacked, and check the score
2022-03-01 restructured database a bit, and made it so that the ship is checked if it is sunk or not
2022-03-04 updated how occupied spaces are tracked
2022-03-04 checks if a ship is sunk or not, and reads json better
2022-03-04 finished attack action
2022-03-06 complete shit
2022-03-06 Added input matrix to battleship board
2022-03-06 save game
2022-03-06 Removed git shenanigans
2022-03-06 success!
2022-03-06 Added header, command text, sick background
2022-03-06 setup other pages
2022-03-07 merch update
2022-03-07 stopping
2022-03-22 place ships
2022-03-22 place ships fixed
2022-03-23 added horizontal and vertical scaling to the ships, and added tests
2022-03-23 Work on main board
2022-03-25 Connected frontend to backend
2022-03-26 the ships, when added to the table, are now added to the database
2022-03-28 changed webapp location
2022-03-28 helped initalize_game.py
2022-03-30 Got schematic to place that can be turned into a ratsnest
2022-04-02 database + backend. This is from the other day but i suck
2022-04-02 Fixed annotations so that button rows are in order
2022-04-02 Added functions to begin placing switches and diodes in a grid
2022-04-03 added in some functionality to let frontend know if move was okay
2022-04-06 updated pcb diagram
2022-04-10 Finished routing
2022-04-13 lol, lmao
2022-04-13 Initial commit (pain) of firmware
2022-04-16 added check game status
2022-04-17 small skeleton to help with working out attack loop logic
2022-04-17 joining games (from web) works now
2022-04-17 aw shit almost done
2022-04-17 adding db so i don't have to try to do that on a remote server
2022-04-17 worker
2022-04-18 added function that gets past game stats (start date and winner)
    also added test function for it, but it is limited, due to my own limited understanding of fixtures, as well as not wanting to make a bunch of default boards
2022-04-18 Refactored ship placement to a semi stable state
2022-04-18 Refactored colors
2022-04-18 created some basic skeletons for the webapp stats pages
2022-04-18 Refactored so Game has Board to allow for States
2022-04-18 a bit more html and js
2022-04-18 Refactored to use PlaceShipState
2022-04-18 pushing for the sake of pushing
2022-04-18 favicon
2022-04-20 Refactored and added attack state
2022-04-20 Fixed hit ships not being marked as hit
2022-04-20 renamed "Bingus" to "testName"
2022-04-20 have the stats table around 90% working
2022-04-20 start game w warboard
2022-04-20 api description
2022-04-22 fixed stats, and made table spacing better by using nbsp characters
2022-04-22 fixed small bug in reporting history vs hardware
2022-04-22 header
2022-04-22 routes
2022-04-22 reddy blur
2022-04-22 nsfw

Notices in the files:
parts and their libraries:
RELEASED UNDER THE CREATIVE COMMONS ATTRIBUTION SHARE-ALIKE 4.0 LICENSE
HTTPS://CREATIVECOMMONS.ORG/LICENSES/BY-SA/4.0
